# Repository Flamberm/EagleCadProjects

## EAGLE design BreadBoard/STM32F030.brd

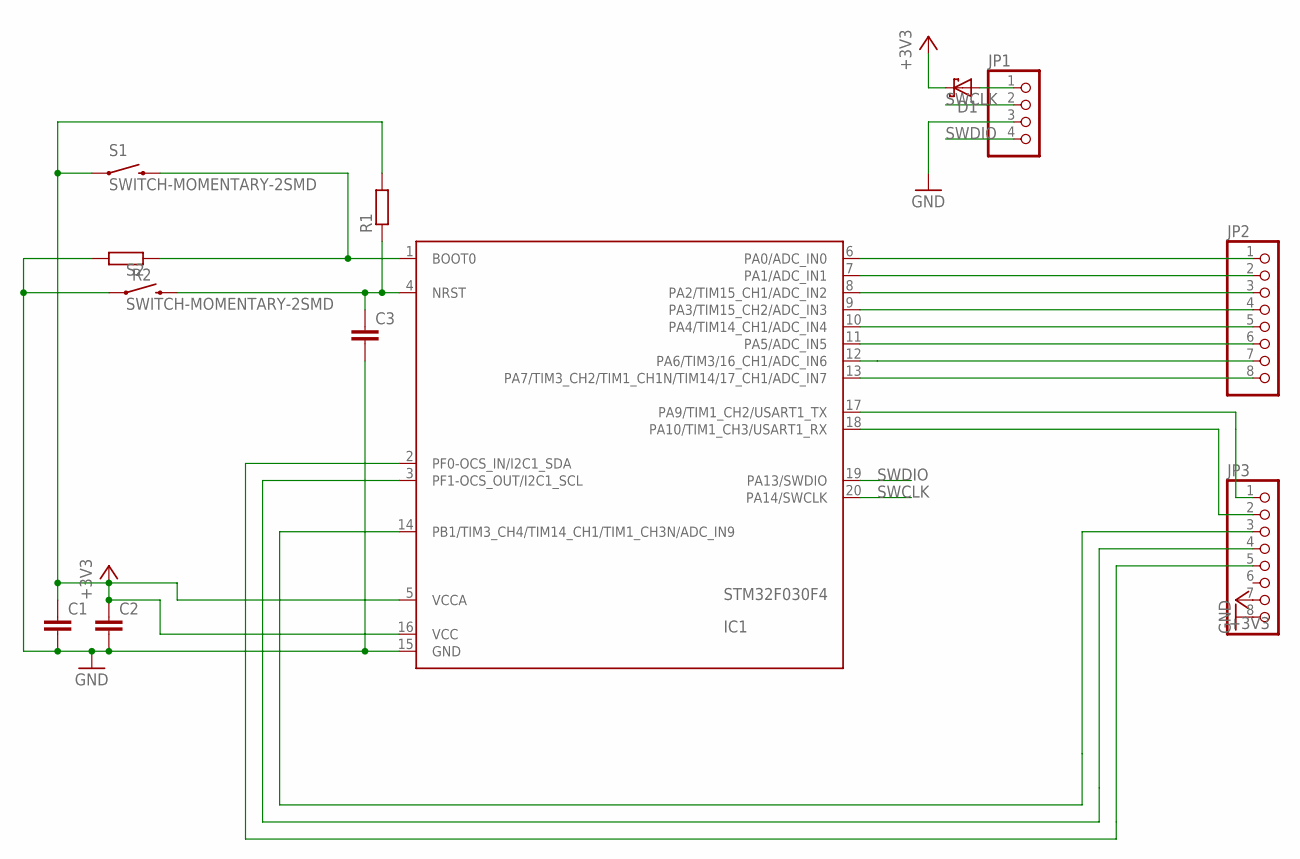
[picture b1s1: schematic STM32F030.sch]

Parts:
C1, C2, C3: CAP_0805; C0805
D1: DIODE-SH_SOD523; SOD523
IC1: STM32F030F4; TSSOP20
JP1: PINHD-1X4; 1X04
JP2, JP3: PINHD-1X8; 1X08
R1, R2: R_0805; R0805
S1, S2: SWITCH-MOMENTARY-2SMD; TACTILE-SWITCH-SMD

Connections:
+3V3: C1.1, C2.1, D1.C, IC1.5 (VCCA), IC1.16 (VCC), JP3.7, R1.2, S1.1
GND: C1.2, C2.2, C3.2, IC1.15 (GND), JP1.3, JP3.8, R2.2, S2.1
unnamed: D1.A, JP1.1
unnamed: IC1.6 (PA0/ADC_IN0), JP2.1
unnamed: IC1.7 (PA1/ADC_IN1), JP2.2
unnamed: C3.1, IC1.4 (NRST), R1.1, S2.3 (2)
unnamed: IC1.1 (BOOT0), R2.1, S1.3 (2)
unnamed: IC1.8 (PA2/TIM15_CH1/ADC_IN2), JP2.3
unnamed: IC1.9 (PA3/TIM15_CH2/ADC_IN3), JP2.4
unnamed: IC1.10 (PA4/TIM14_CH1/ADC_IN4), JP2.5
unnamed: IC1.11 (PA5/ADC_IN5), JP2.6
unnamed: IC1.12 (PA6/TIM3/16_CH1/ADC_IN6), JP2.7
unnamed: IC1.13 (PA7/TIM3_CH2/TIM1_CH1N/TIM14/17_CH1/ADC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), JP2.8
unnamed: IC1.17 (PA9/TIM1_CH2/USART1_TX), JP3.1
unnamed: IC1.18 (PA10/TIM1_CH3/USART1_RX), JP3.2
unnamed: IC1.2 (PF0-OCS_IN/I2C1_SDA), JP3.5
unnamed: IC1.3 (PF1-OCS_OUT/I2C1_SCL), JP3.4
unnamed: IC1.14 (PB1/TIM3_CH4/TIM14_CH1/TIM1_CH3N/ADC_IN9), JP3.3
SWCLK: IC1.20 (PA14/SWCLK), JP1.2
SWDIO: IC1.19 (PA13/SWDIO), JP1.4

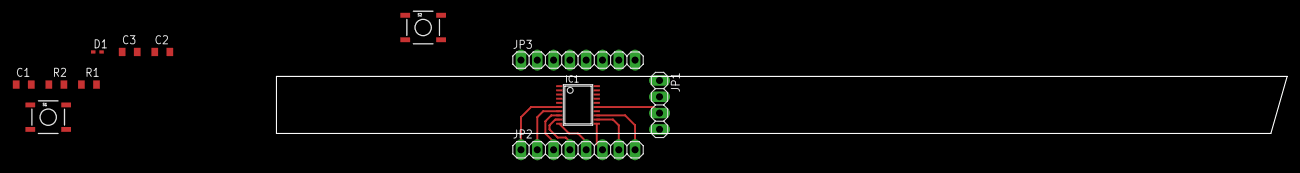
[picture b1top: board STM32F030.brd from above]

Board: 2 copper layers, 12 parts (0 on the bottom side), 20 nets.

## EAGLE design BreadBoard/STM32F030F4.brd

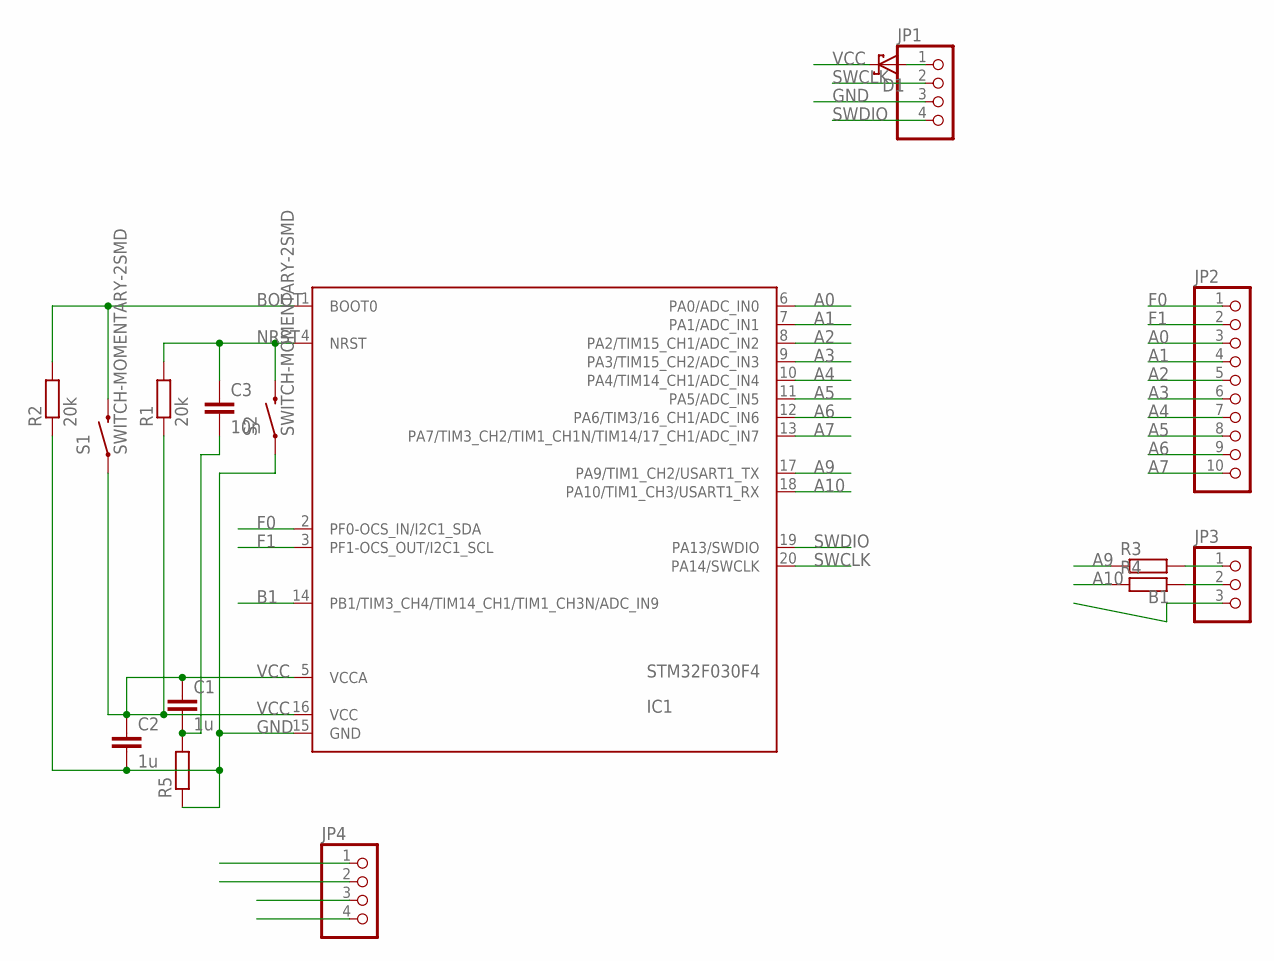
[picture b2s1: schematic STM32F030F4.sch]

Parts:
C1, C2: 1u; C1206
C3: 10n; C1206
D1: DIODE-SH_SOD523; SOD523
IC1: STM32F030F4; TSSOP20
JP1, JP4: PINHD-1X4; 1X04
JP2: PINHD-1X10; 1X10
JP3: PINHD-1X3; 1X03
R1, R2: 20k; R1206
R3, R4, R5: R_1206; R1206
S1, S2: SWITCH-MOMENTARY-2SMD; TACTILE-SWITCH-SMD

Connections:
A0: IC1.6 (PA0/ADC_IN0), JP2.3
A1: IC1.7 (PA1/ADC_IN1), JP2.4
A2: IC1.8 (PA2/TIM15_CH1/ADC_IN2), JP2.5
A3: IC1.9 (PA3/TIM15_CH2/ADC_IN3), JP2.6
A4: IC1.10 (PA4/TIM14_CH1/ADC_IN4), JP2.7
A5: IC1.11 (PA5/ADC_IN5), JP2.8
A6: IC1.12 (PA6/TIM3/16_CH1/ADC_IN6), JP2.9
A7: IC1.13 (PA7/TIM3_CH2/TIM1_CH1N/TIM14/17_CH1/ADC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), JP2.10
A9: IC1.17 (PA9/TIM1_CH2/USART1_TX), R3.1
A10: IC1.18 (PA10/TIM1_CH3/USART1_RX), R4.1
B1: IC1.14 (PB1/TIM3_CH4/TIM14_CH1/TIM1_CH3N/ADC_IN9), JP3.3
BOOT: IC1.1 (BOOT0), R2.2, S1.3 (2)
F0: IC1.2 (PF0-OCS_IN/I2C1_SDA), JP2.1
F1: IC1.3 (PF1-OCS_OUT/I2C1_SCL), JP2.2
GND: C2.2, IC1.15 (GND), JP1.3, JP4.3, JP4.4, R2.1, R5.1, S2.1
unnamed: D1.A, JP1.1
unnamed: JP3.1, R3.2
unnamed: JP3.2, R4.2
unnamed: C1.2, C3.2, R5.2
NRST: C3.1, IC1.4 (NRST), R1.2, S2.3 (2)
SWCLK: IC1.20 (PA14/SWCLK), JP1.2
SWDIO: IC1.19 (PA13/SWDIO), JP1.4
VCC: C1.1, C2.1, D1.C, IC1.5 (VCCA), IC1.16 (VCC), JP4.1, JP4.2, R1.1, S1.1

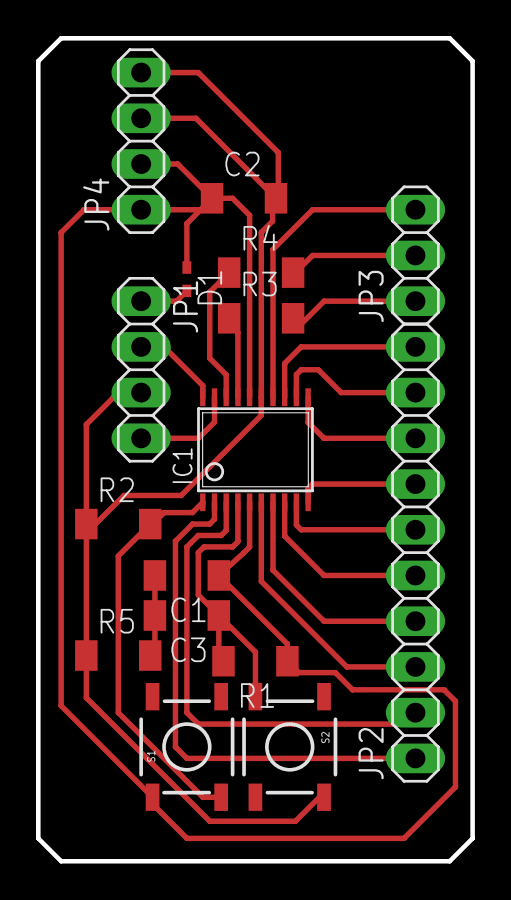
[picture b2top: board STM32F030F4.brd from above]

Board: 2 copper layers, 24.1 x 45.7 mm, 16 parts (0 on the bottom side), 23 nets.

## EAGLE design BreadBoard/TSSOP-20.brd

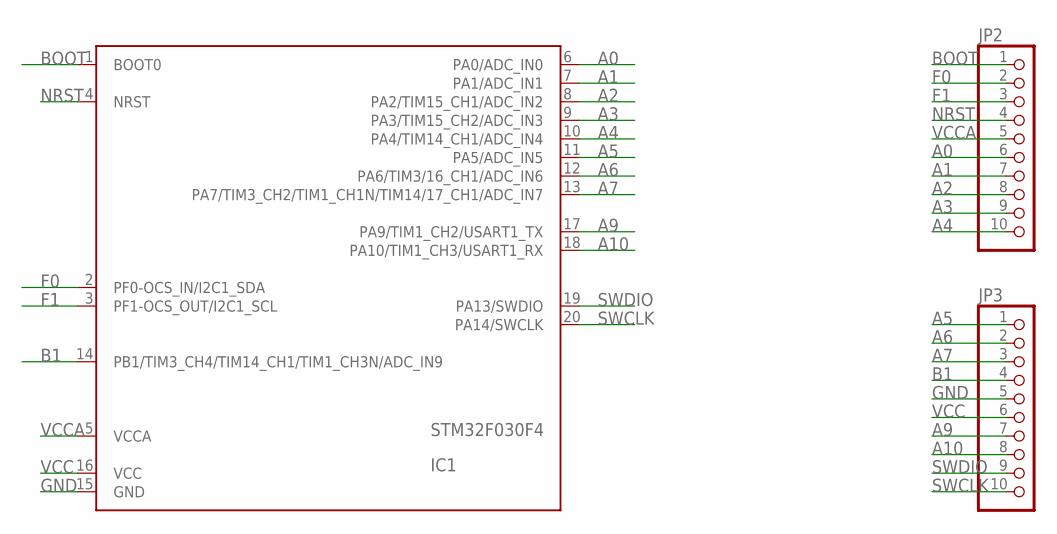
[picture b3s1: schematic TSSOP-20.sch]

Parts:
IC1: STM32F030F4; TSSOP20
JP2, JP3: PINHD-1X10; 1X10

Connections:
A0: IC1.6 (PA0/ADC_IN0), JP2.6
A1: IC1.7 (PA1/ADC_IN1), JP2.7
A2: IC1.8 (PA2/TIM15_CH1/ADC_IN2), JP2.8
A3: IC1.9 (PA3/TIM15_CH2/ADC_IN3), JP2.9
A4: IC1.10 (PA4/TIM14_CH1/ADC_IN4), JP2.10
A5: IC1.11 (PA5/ADC_IN5), JP3.1
A6: IC1.12 (PA6/TIM3/16_CH1/ADC_IN6), JP3.2
A7: IC1.13 (PA7/TIM3_CH2/TIM1_CH1N/TIM14/17_CH1/ADC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), JP3.3
A9: IC1.17 (PA9/TIM1_CH2/USART1_TX), JP3.7
A10: IC1.18 (PA10/TIM1_CH3/USART1_RX), JP3.8
B1: IC1.14 (PB1/TIM3_CH4/TIM14_CH1/TIM1_CH3N/ADC_IN9), JP3.4
BOOT: IC1.1 (BOOT0), JP2.1
F0: IC1.2 (PF0-OCS_IN/I2C1_SDA), JP2.2
F1: IC1.3 (PF1-OCS_OUT/I2C1_SCL), JP2.3
GND: IC1.15 (GND), JP3.5
NRST: IC1.4 (NRST), JP2.4
SWCLK: IC1.20 (PA14/SWCLK), JP3.10
SWDIO: IC1.19 (PA13/SWDIO), JP3.9
VCC: IC1.16 (VCC), JP3.6
VCCA: IC1.5 (VCCA), JP2.5

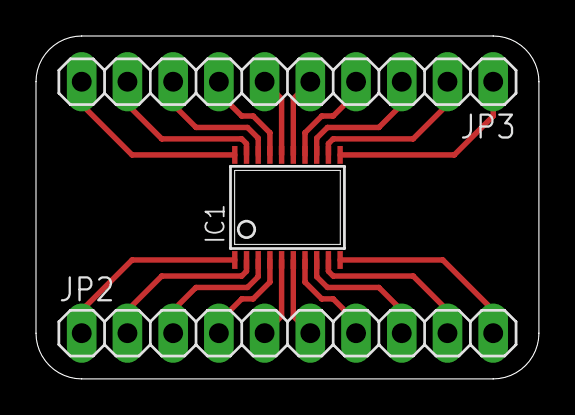
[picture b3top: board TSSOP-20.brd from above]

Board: 2 copper layers, 27.9 x 19.1 mm, 3 parts (0 on the bottom side), 20 nets.

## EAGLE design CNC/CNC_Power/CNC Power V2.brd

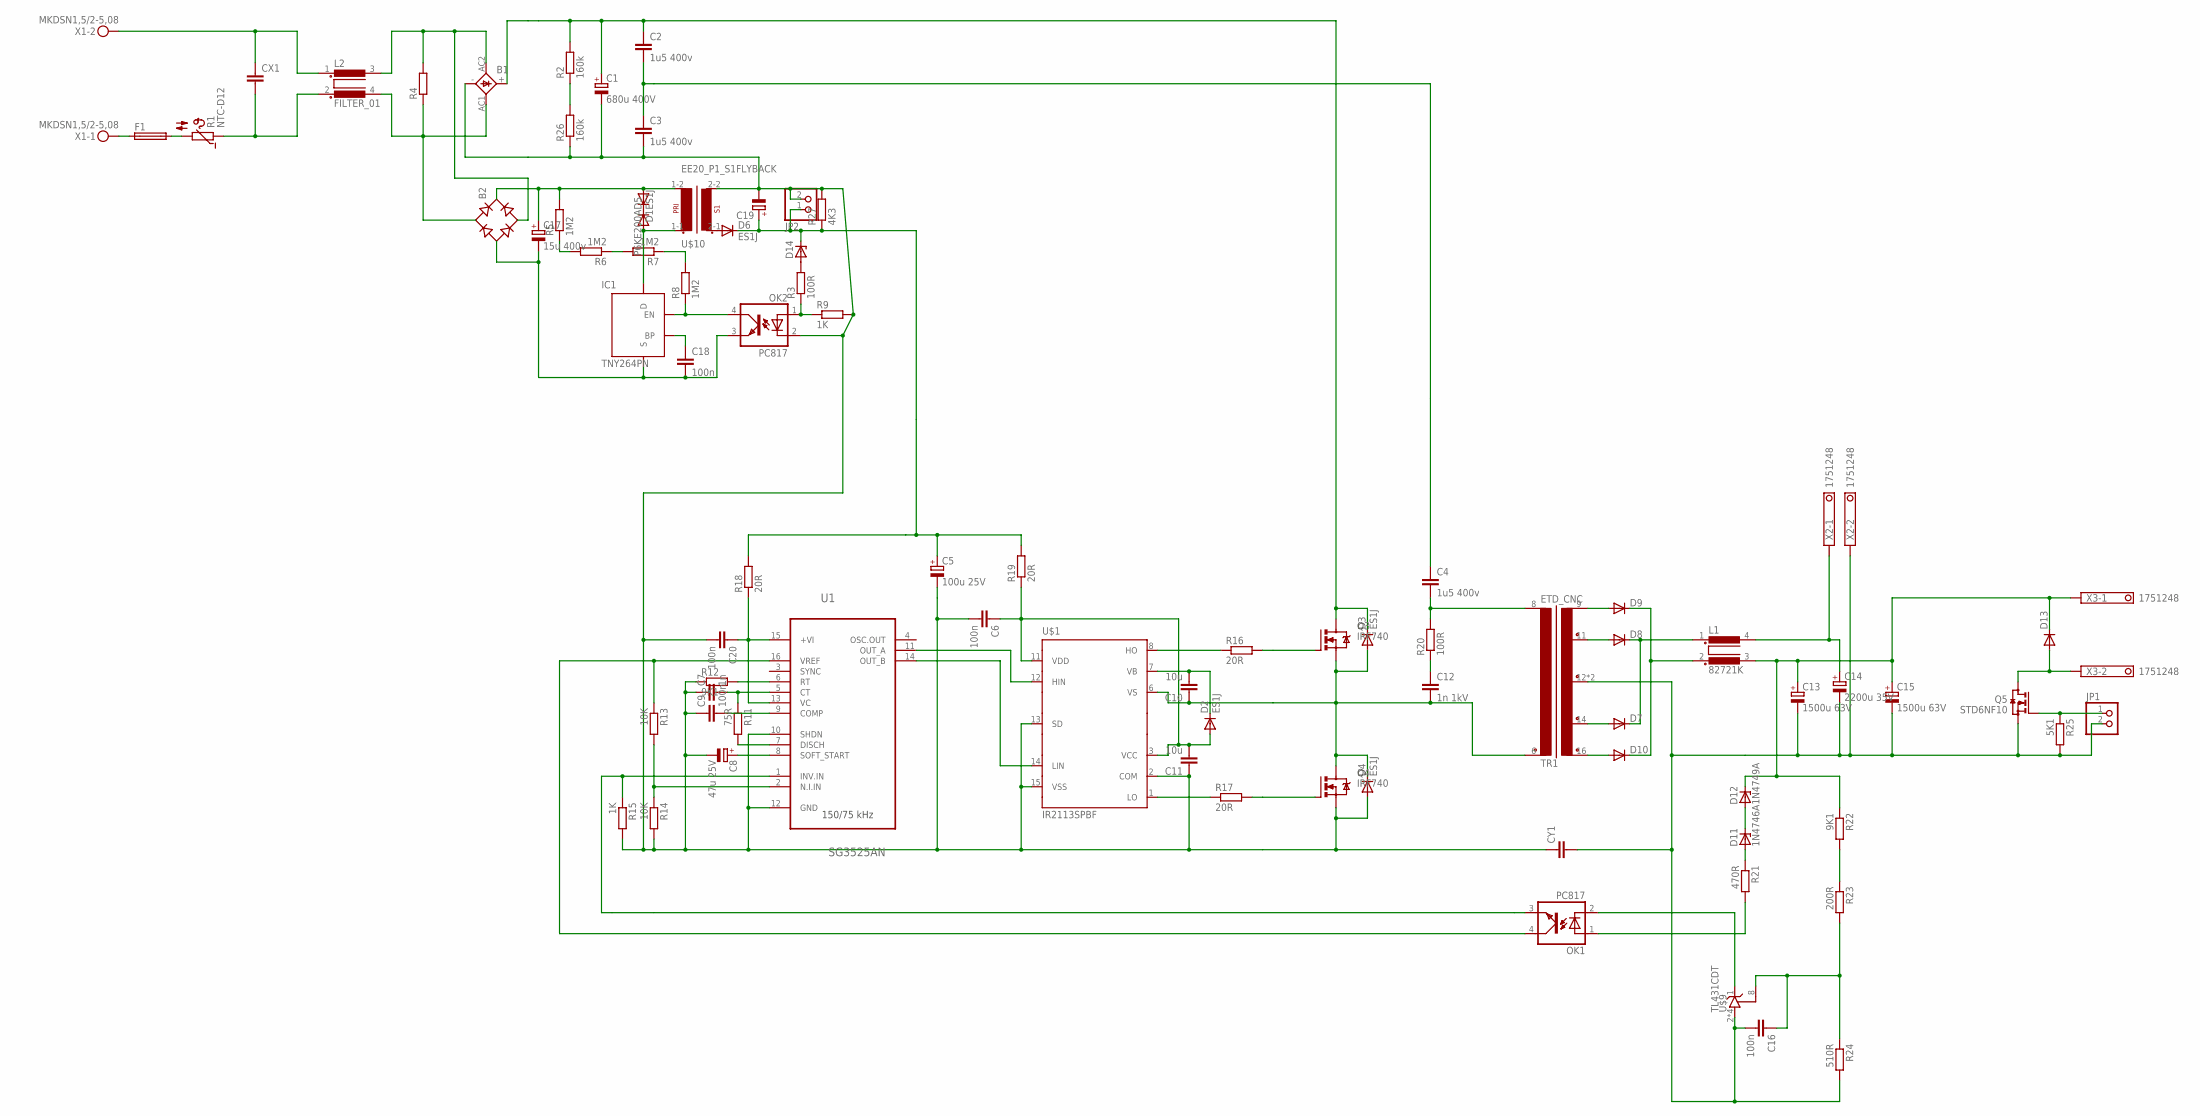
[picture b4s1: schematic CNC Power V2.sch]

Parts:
B1: KBL
B2: RB1A
C1: 680u 400V; EB35D
C2, C3, C4: 1u5 400v; C225-074X268
C5: 100u 25V; E2,5-7
C6, C9, C16, C18, C20: 100n; C0805
C7: 1n; C0805
C8: 47u 25V; E2,5-7
C10, C11: 10u; C0805
C12: 1n 1kV; C050-025X075
C13, C15: 1500u 63V; E7,5-18
C14: 2200u 35V; E7,5-18
C17: 15u 400v; E5-13
C19: CPOL-EUE2.5-7; E2,5-7
CX1: CXXC15B8; XC15B8
CY1: CYYC10B4; YC10B4
D1: P6KE200A; DO204-10
D2, D3, D4, D5, D6: ES1J; DO214AC
D7, D8, D9, D10, D13: DIODE-DO220S; DO220S
D11: 1N4746A; DO41Z10
D12: 1N4749A; DO41Z10
D14: ZENER-DIODEDO41Z10; DO41Z10
F1: SH22,5
IC1: TNY264PN; DIP-8B
JP1, JP2: PINHD-1X2; 1X02
L1: 82721K
L2: FILTER_01; 82721K
OK1, OK2: PC817; DIL04
Q3, Q4: IRF740; TO220BV
Q5: STD6NF10; DPAK
R1: NTC-D12
R2, R26: 160k; 0207/10
R3: 100R; R0805
R4: R-EU_0309/10; 0309/10
R5, R6, R7, R8: 1M2; R0805
R9, R15: 1K; R0805
R11: 75R; R0805
R12, R22: 9K1; R0805
R13, R14: 10K; R0805
R16, R17: 20R; 0309/12
R18, R19: 20R; R2512
R20: 100R; 0617/17
R21: 470R; R0805
R23: 200R; R0805
R24: 510R; R0805
R25: 5K1; R0805
R27: 4K3; R0805
TR1: ETD_CNC; ETD39_16PIN
U1: SG3525AN; DIP254P762X510-16
U$1: IR2113SPBF; SO16W
U$9: TL431CDT; SO8
U$10: EE20_P1_S1FLYBACK; EE20_P1_S1-REV-4PIN
X1: MKDSN1,5/2-5,08
X2, X3: 1751248

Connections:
HV-0: B1.-, C1.-, C3.2, C5.-, C6.2, C7.1, C8.-, C9.1, C11.1, C19.-, C20.2, CY1.1, D4.A, JP2.2, OK2.2 (C), Q4.S, R9.2, R12.1, R14.2, R15.2, R26.1, R27.2, U1.10 (SHDN), U1.12 (GND), U$1.2 (COM), U$1.13 (SD), U$1.15 (VSS), U$10.2-2 (S1-2)
HV-150: C2.2, C3.1, C4.1
HV-300: B1.+, C1.+, C2.1, D3.C, Q3.D, R2.2
unnamed: F1.1, X1.1
unnamed: F1.2, R1.2
unnamed: CX1.2, L2.2 (3), R1.1
unnamed: D7.A, TR1.14 (S2-1)
unnamed: R16.1, U$1.8 (HO)
unnamed: R17.1, U$1.1 (LO)
unnamed: Q3.G, R16.2
unnamed: OK1.3 (EMIT), R15.1, U1.1 (INV.IN)
unnamed: C4.2, R20.2, TR1.8 (P1-2)
unnamed: C20.1, R18.1, U1.13 (VC), U1.15 (+VI)
unnamed: B1.AC1 (AC2), B2.AC1, L2.4, R4.1
unnamed: CX1.1, L2.1, X1.2
unnamed: B2.-, C17.-, C18.2, IC1.2 (S), IC1.3 (S), IC1.7 (S), IC1.8 (S), OK2.3 (EMIT)
unnamed: B1.AC2 (AC1), B2.AC2, L2.3 (2), R4.2
unnamed: C7.2, R11.1, U1.5 (CT)
unnamed: R11.2, U1.7 (DISCH)
unnamed: Q4.G, R17.2
unnamed: U1.11 (OUT_A), U$1.12 (HIN)
unnamed: U1.14 (OUT_B), U$1.14 (LIN)
unnamed: R12.2, U1.6 (RT)
unnamed: C8.+, U1.8 (SOFT_START)
unnamed: C9.2, U1.9 (COMP)
unnamed: OK1.4 (COL), R13.1, U1.16 (VREF)
unnamed: R13.2, R14.1, U1.2 (N.I.IN)
unnamed: IC1.4 (EN), OK2.4 (COL), R8.1
unnamed: D10.A, TR1.16 (S1-1)
unnamed: D8.A, TR1.11 (S2-2)
unnamed: R5.1, R6.2
unnamed: R6.1, R7.2
unnamed: C12.1, R20.1
unnamed: D9.A, TR1.9 (S1-2)
unnamed: D7.C, D8.C, L1.1
unnamed: D9.C, D10.C, L1.2 (3)
unnamed 36: C13.-, C14.-, C15.-, C16.2, CY1.2, JP1.2, Q5.S, R24.2, R25.2, TR1.12 (S0), TR1.13 (S0), U$9.2 (A), U$9.3 (A), U$9.6 (A), U$9.7 (A), X2.2; also elsewhere on the board
unnamed 37: C14.+, L1.4 (2), X2.1; also elsewhere on the board
unnamed: C13.+, C15.+, D12.C, D13.C, L1.3 (4), R22.1, X3.1
unnamed: D11.C, D12.A
unnamed: D11.A, R21.1
unnamed: OK1.1 (A), R21.2
unnamed: OK1.2 (C), U$9.1 (C)
unnamed: C16.1, R23.2, R24.1, U$9.8 (R)
unnamed: R22.2, R23.1
unnamed: JP1.1, Q5.G, R25.1
unnamed: R2.1, R26.2
unnamed: D13.A, Q5.D, X3.2
unnamed: C5.+, C19.+, D6.C, D14.C, JP2.1, R18.2, R19.2, R27.1
unnamed: R7.1, R8.2
unnamed: D1.C, D5.C
unnamed: D5.A, IC1.5 (D), U$10.1-1
unnamed: D14.A, R3.2
unnamed: C18.1, IC1.1 (BP)
unnamed: B2.+, C17.+, D1.A, R5.2, U$10.1-2
unnamed: D6.A, U$10.2-1 (S1-1)
unnamed: OK2.1 (A), R3.1, R9.1
VB: C10.2, D2.C, U$1.7 (VB)
VCC: C6.1, C11.2, D2.A, R19.1, U$1.3 (VCC), U$1.11 (VDD)
VS: C10.1, C12.2, D3.A, D4.C, Q3.S, Q4.D, TR1.6 (P1-1), U$1.6 (VS)

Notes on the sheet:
150/75 kHz

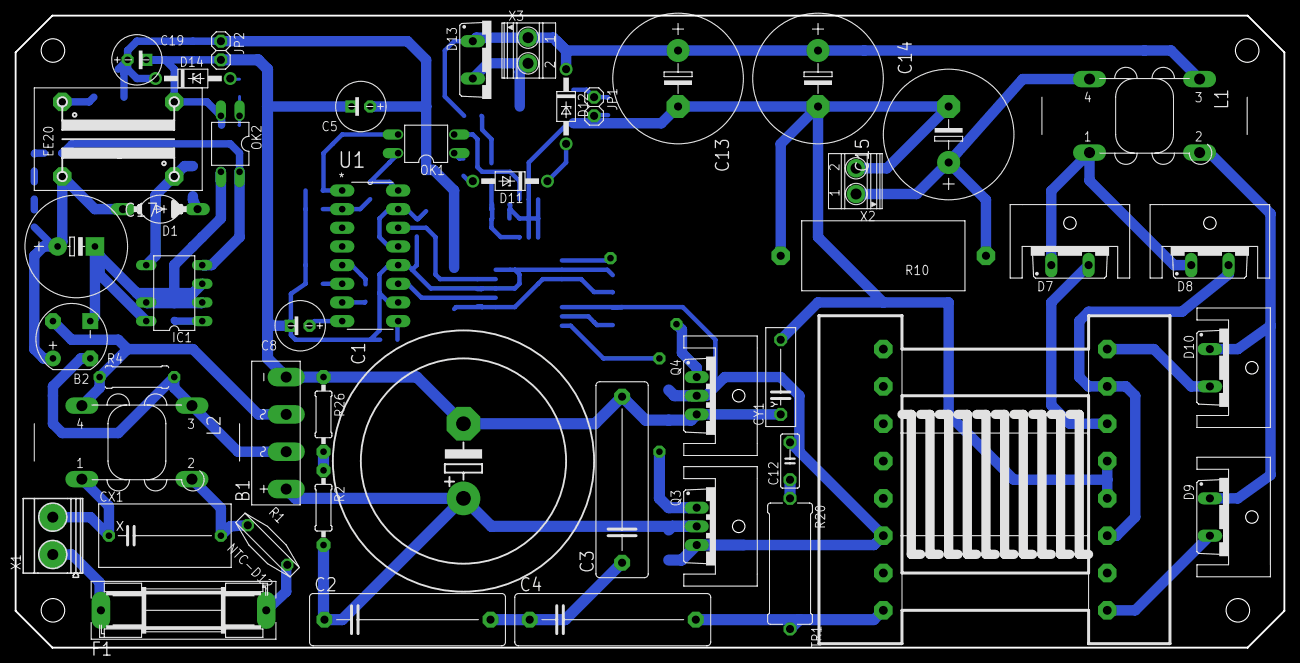
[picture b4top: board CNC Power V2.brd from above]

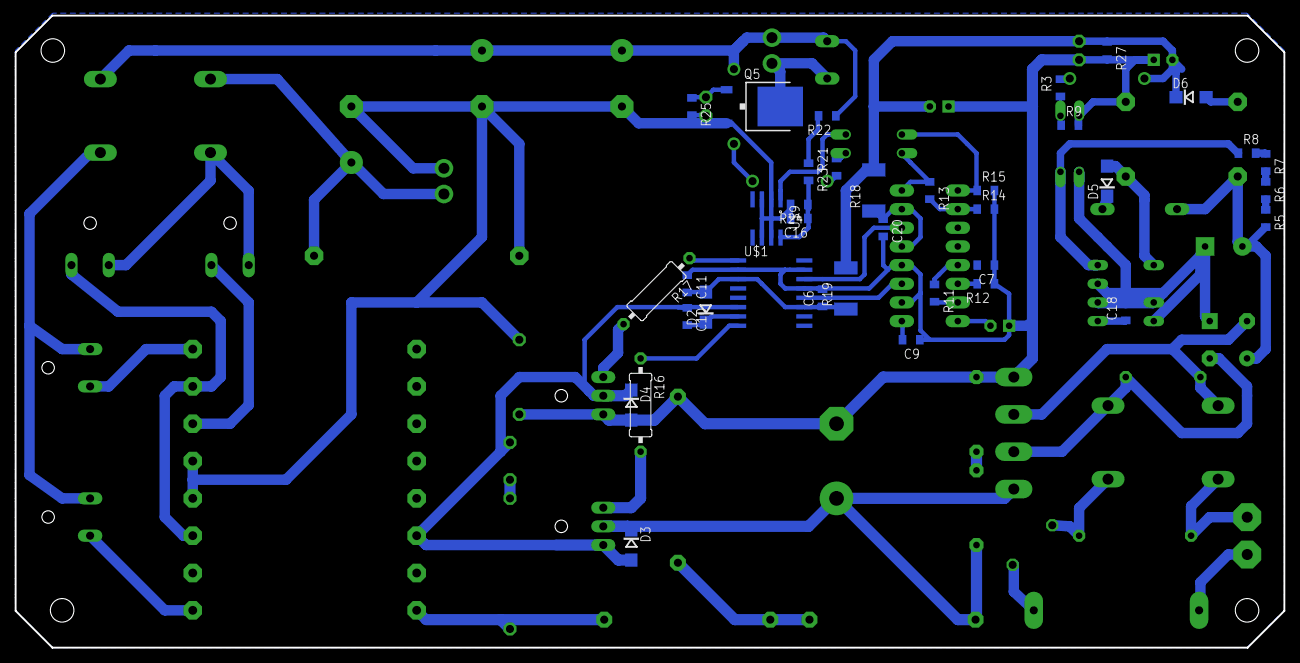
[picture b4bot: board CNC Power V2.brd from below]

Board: 2 copper layers, 172.7 x 86.0 mm, 90 parts (37 on the bottom side), 60 nets.

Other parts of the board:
R10: 100R; SQP-5
U$3, U$4, U$5, U$6, U$7, U$8: SK95-3M3_HOLE

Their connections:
unnamed 36: R10.2; also elsewhere on the board
unnamed 37: R10.1; also elsewhere on the board

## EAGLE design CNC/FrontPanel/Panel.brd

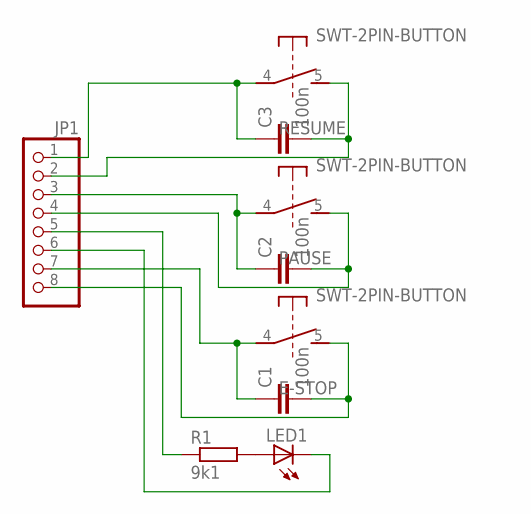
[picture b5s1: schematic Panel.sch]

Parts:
C1, C2, C3: 100n; C0805
E-STOP: SWT-2PIN-BUTTON; SWT-2-2PIN-WBUTTON
JP1: PINHD-1X8/90; 1X08/90
LED1: LED3MM
PAUSE: SWT-2PIN-BUTTON; SWT-2-2PIN-WBUTTON
R1: 9k1; R0805
RESUME: SWT-2PIN-BUTTON; SWT-2-2PIN-WBUTTON

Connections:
unnamed: LED1.A, R1.2
unnamed: C1.1, E-STOP.4 (2), JP1.7
unnamed: C1.2, E-STOP.5 (3), JP1.8
unnamed: C2.1, JP1.3, PAUSE.4 (2)
unnamed: C2.2, JP1.4, PAUSE.5 (3)
unnamed: C3.1, JP1.1, RESUME.4 (2)
unnamed: C3.2, JP1.2, RESUME.5 (3)
unnamed: JP1.5, R1.1
unnamed: JP1.6, LED1.K (C)

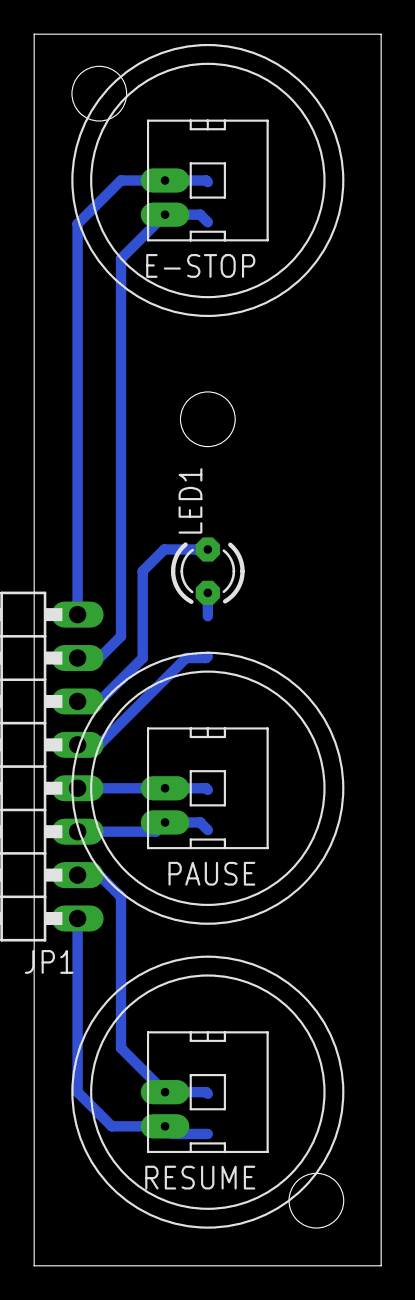
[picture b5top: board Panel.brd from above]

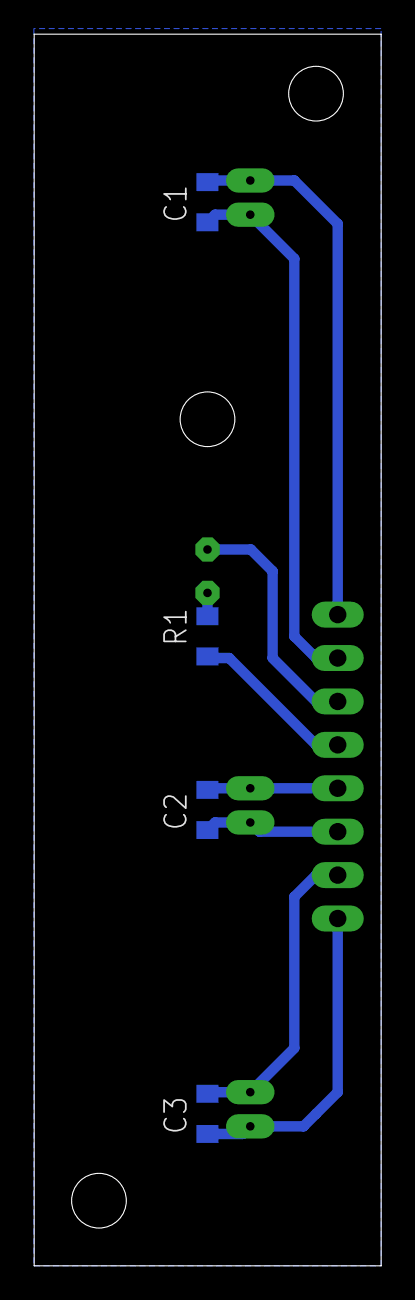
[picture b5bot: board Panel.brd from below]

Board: 2 copper layers, 20.3 x 72.1 mm, 9 parts (4 on the bottom side), 9 nets.

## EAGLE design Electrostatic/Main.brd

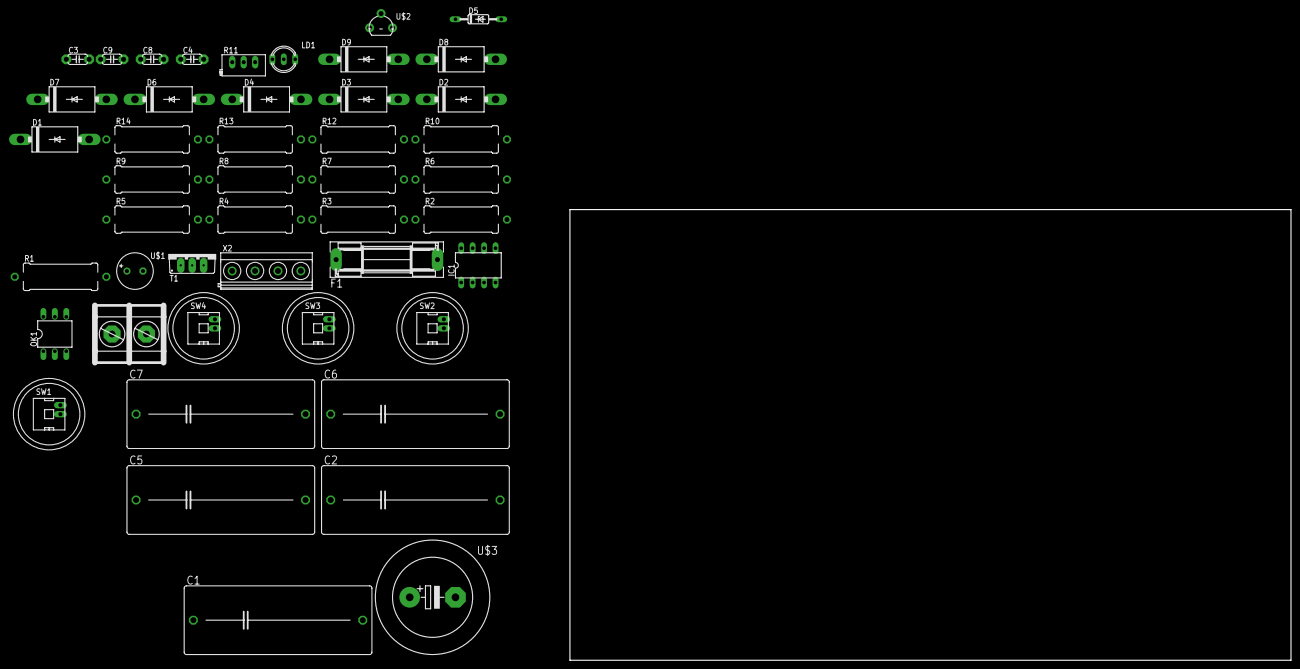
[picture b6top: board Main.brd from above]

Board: 2 copper layers, 160.0 x 100.0 mm, 46 parts (0 on the bottom side), 33 nets, no tracks yet.

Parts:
C1: 100n 400v; C375-155X418
C2: 330n 400v; C375-155X418
C3: 0.22uF; C050-024X044
C4: 3n3 2KV; C050-024X044
C5: 1.5uF 400v; C375-155X418
C6, C7: 33n 400v; C375-155X418
C8, C9: 6n8 1KV; C050-024X044
D1, D2, D3, D4, D6, D7, D8, D9: DO201-15
D5: 5v1; DO35Z10
F1: SH22,5
IC1: TINY13-20PU; DIL08
LD1: DUOLED-C-5MM
OK1: MOC3043M; DIL06
R1, R2, R10, R14: 27R; MF-2
R3: MF-2
R4: 180R; MF-2
R5, R6, R7, R9, R13: 820R; MF-2
R8: 560R; MF-2
R11: RJ9W
R12: 33K; MF-2
SW1, SW2, SW3, SW4: SW-SWT-2PIN-BUTTON; SWT-2-2PIN-WBUTTON
T1: BT138-V; TO220BV
U$1: 220uF 16v; E3,5-8
U$2: TRANS-NPN; SOT-92WIDE
U$3: CAP-POL_E25-10-C; C_D25-G10-CLAMP
X1: CON-7.62-02P; KF25C-7.62-02P-13
X2: MKDSN1,5/4-5,08

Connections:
unnamed: C1.1, R2.1, SW1.4
unnamed: C1.2, R1.2, X1.P$1
unnamed: F1.2, X1.P$2
unnamed: IC1.5, LD1.AX
unnamed: C2.2, R1.1, R3.1, SW2.5
unnamed: C2.1, D1.A, D2.C, R3.2
unnamed: IC1.6, LD1.AR
unnamed: D3.A, D4.C, F1.1, SW1.5
unnamed: C3.2, D2.A, D4.A, D5.A, IC1.2, IC1.4, R5.2, R6.2, R7.1, U$1.-
unnamed: D1.C, D3.C, R4.1
unnamed: R5.1, SW3.5
unnamed: LD1.C, R6.1
unnamed: C3.1, D5.C, IC1.1, IC1.8, R4.2, U$1.+
unnamed: R7.2, SW4.4
unnamed: IC1.7, SW3.4
unnamed: OK1.2, SW4.5
unnamed: IC1.3, R8.2
unnamed: OK1.1, R8.1
unnamed: OK1.4, T1.G
unnamed: C4.2, R9.1, SW2.4, T1.T2
unnamed: C4.1, C5.2, R10.1, T1.T1
unnamed: OK1.6, R9.2
unnamed: C5.1, D7.C, D8.A, R10.2
unnamed: D6.C, D9.A, R2.2
unnamed: D6.A, D7.A, R11.B, R11.W, U$3.+, X2.1
unnamed: R11.A, R12.2
unnamed: C9.2, R12.1, R13.2, U$2.B
unnamed: R13.1, X2.2
unnamed: C7.1, D8.C, D9.C, U$3.-
unnamed: C6.1, C8.2, C9.1, U$2.E
unnamed: C6.2, X2.3
unnamed: R14.1, U$2.C
unnamed: C7.2, C8.1, R14.2, X2.4

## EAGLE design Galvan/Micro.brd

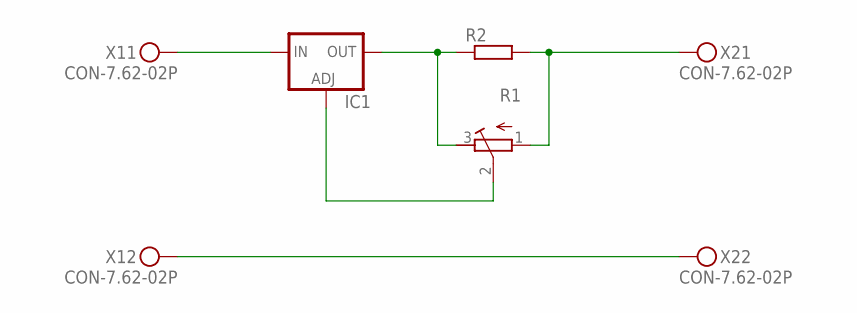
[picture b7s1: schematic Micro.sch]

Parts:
IC1: LM350T; 317TS
R1: R_POTE; EVUE
R2: R_SQP-5; SQP-5
X1, X2: CON-7.62-02P; KF25C-7.62-02P-13

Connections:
unnamed: IC1.2 (OUT), R1.3 (E), R2.1
unnamed: R1.1 (A), R2.2, X2.P$1
unnamed: IC1.1 (ADJ), R1.2 (S)
unnamed: X1.P$2, X2.P$2
unnamed: IC1.3 (IN), X1.P$1

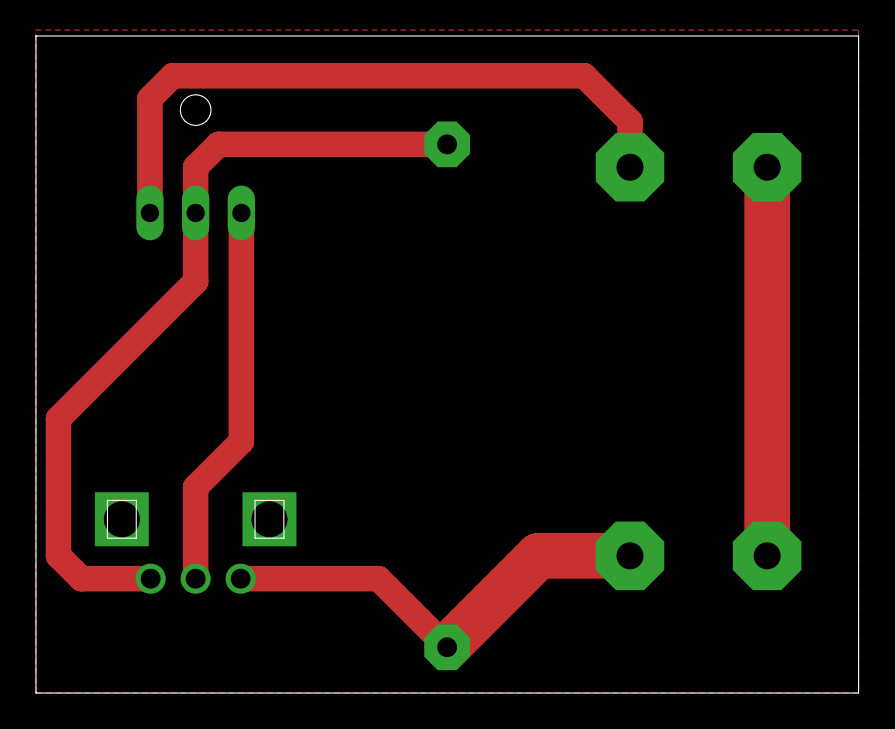
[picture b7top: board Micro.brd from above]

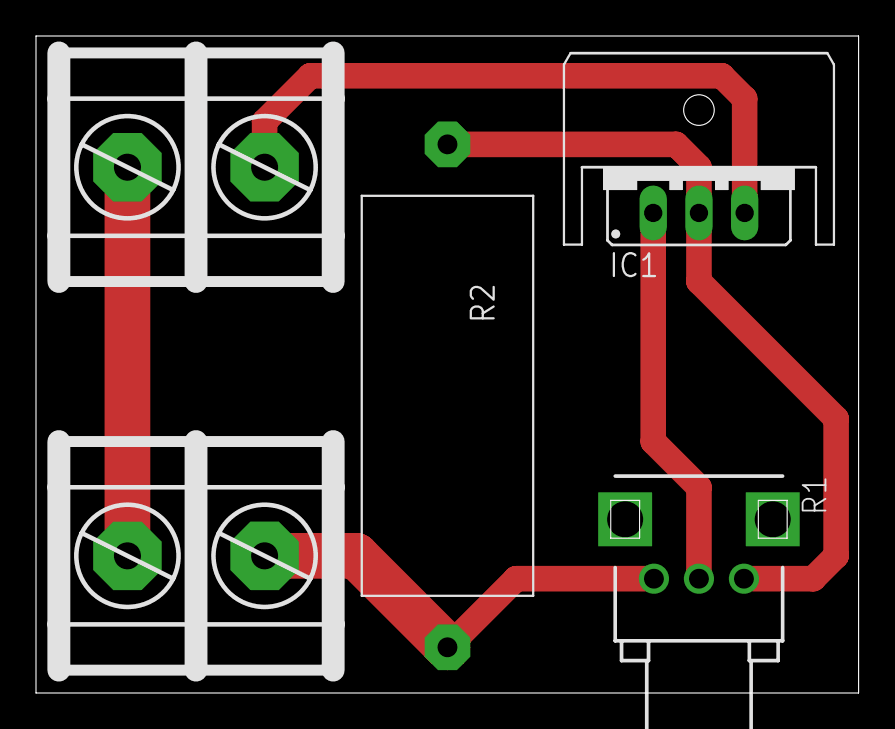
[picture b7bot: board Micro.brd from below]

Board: 2 copper layers, 45.7 x 36.5 mm, 6 parts (6 on the bottom side), 5 nets.

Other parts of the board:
U$1: SK95-3M3_HOLE

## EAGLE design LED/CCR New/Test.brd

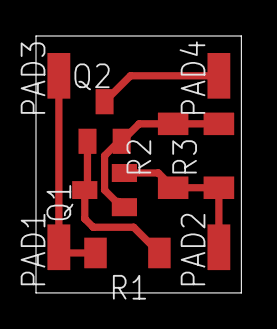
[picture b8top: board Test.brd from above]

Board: 2 copper layers, 11.4 x 14.3 mm, 9 parts (0 on the bottom side), 5 nets.

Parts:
PAD1, PAD2, PAD3, PAD4: SMD1,27-2,54
Q1, Q2: BC817-40LT1SMD; SOT23-BEC
R1: 30R; R1206
R2, R3: 10R; R1206

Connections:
unnamed: PAD1.1, PAD3.1, R1.2
unnamed: Q1.C, Q2.B, R1.1
unnamed: PAD4.1, Q2.C
unnamed: PAD2.1, Q1.E, R2.1, R3.1
unnamed: Q1.B, Q2.E, R2.2, R3.2

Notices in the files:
parts and their libraries:
SparkFun-Electromechanical: Licensing: Creative Commons ShareAlike 4.0 International - https://creativecommons.org/licenses/by-sa/4.0
